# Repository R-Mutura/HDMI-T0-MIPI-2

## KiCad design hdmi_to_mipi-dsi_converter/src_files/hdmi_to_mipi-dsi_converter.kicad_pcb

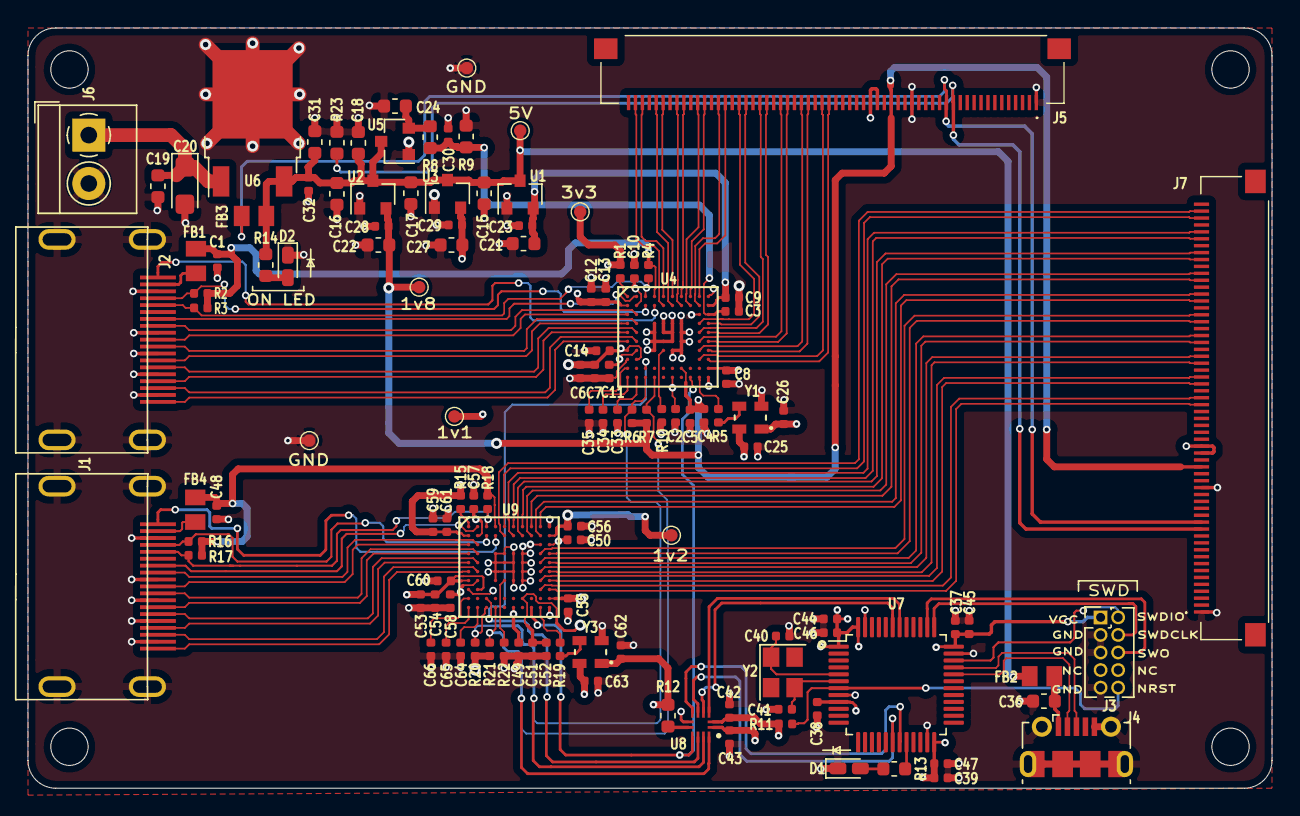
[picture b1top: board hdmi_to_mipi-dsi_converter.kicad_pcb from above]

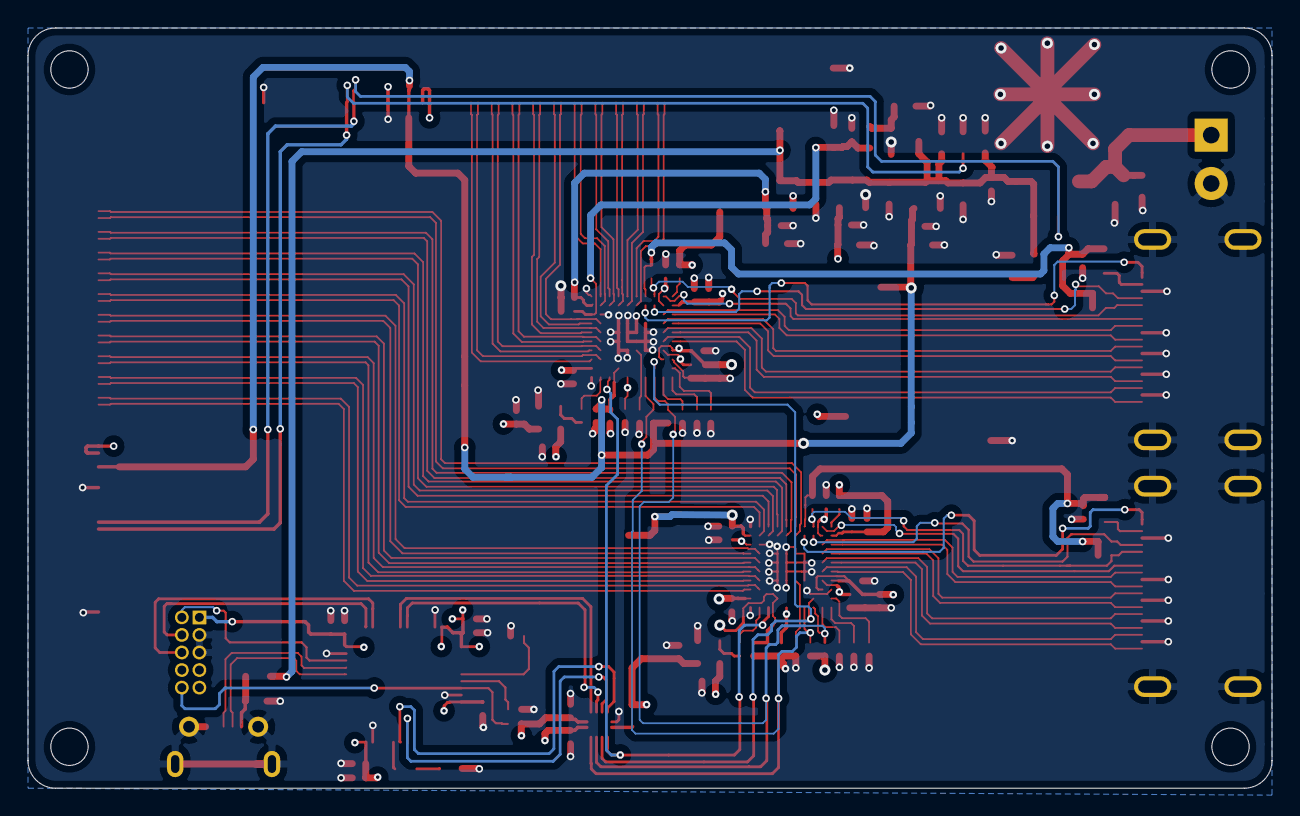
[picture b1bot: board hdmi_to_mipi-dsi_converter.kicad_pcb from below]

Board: 4 copper layers, 90.0 x 55.0 mm, 125 parts (4 on the bottom side), 113 nets.

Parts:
C1, C3, C5, C7, C9, C11, C13, C14, C32, C48, C50, C52, C54, C56, C58, C60, C61: 10n; C_0402_1005Metric
C2, C4, C6, C8, C10, C12, C23, C25, C28, C29, C30, C33, C34, C35, C37, C38, C39, C42, C43, C49, C51, C53, C55, C57, C59, C62, C64, C65, C66: 0.1u; C_0402_1005Metric
C15, C16, C17, C18, C21, C22, C24, C27, C36: 10u; C_0603_1608Metric
C19, C31: 0.1u; C_0603_1608Metric
C20: 10u; CP_EIA-3216-18_Kemet-A
C26, C63: 0.01u; C_0402_1005Metric
C40, C41: 18p; C_0402_1005Metric
C44, C45: 10u; C_0402_1005Metric
C46, C47: 4.7u; C_0402_1005Metric
D1, D2: LED_Small; LED_0603_1608Metric_Castellated
FB1, FB4: Ferrite_Bead_Small; BEADC2012X105N
FB2, FB3: BLM21PG220SN1; BEADC2012X105N
H1, H2, H3, H4: MountingHole; MountingHole_2.7mm_M2.5
J1, J2: HDMI-019S
J3: Conn_02x05_Odd_Even; PinHeader_2x05_P1.27mm_Vertical
J4: USB_B_Micro; USB_Micro-B_Molex-105017-0001
J5, J7: XF2M60151AH
J6: Conn_01x02; TerminalBlock_4Ucon_1x02_P3.50mm_Horizontal
R1, R10, R15, R22: 2k; R_0402_1005Metric
R2, R3, R4, R16, R17, R18: 47k; R_0402_1005Metric
R5, R19: 33R; R_0402_1005Metric
R6, R7, R11, R20, R21: 10k; R_0402_1005Metric
R8: 4k; R_0603_1608Metric
R9: 2k; R_0603_1608Metric
R12: 47k; R_0603_1608Metric
R13, R14: 1k; R_0603_1608Metric
R23: 0R; R_0603_1608Metric
TP1, TP2, TP3, TP4, TP5, TP6, TP7: TestPoint; TestPoint_Pad_D0.9mm
U1: MCP1700-1202E_SOT23; SOT-23
U2: MCP1700-1802E_SOT23; SOT-23
U3, U5: MCP1700-3302E_SOT23; SOT-23
U4, U9: TC358870XBG_NOK_; VFBGA-80_7x7mm_Pitch0.65mm
U6: MC78M05_TO252; TO-252-2
U7: STM32F103C8Tx; LQFP-48_7x7mm_P0.5mm
U8: FXMA2104UMX; QFN40P180X180X55-12N
Y1, Y3: CRYSTAL_48MHZ; DSC6101JI2A-048.0000
Y2: 8MHz; Crystal_SMD_3225-4Pin_3.2x2.5mm

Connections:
+1V1: C2.1, C3.1, C10.1, C11.1, C30.1, C49.1, C50.1, C57.1, C58.1, R8.2, R9.1, TP5.1, U4.B2, U4.C10, U4.G2, U4.K6, U9.B2, U9.C10, U9.G2, U9.K6
+1V2: C8.1, C9.1, C21.1, C23.1, C55.1, C56.1, TP7.1, U1.2, U4.B10, U4.J10, U9.B10, U9.J10
+1V8: C4.1, C5.1, C22.1, C28.1, C43.1, C51.1, C52.1, J5.22, J7.22, R6.2, R7.2, R20.2, R21.2, TP6.1, U2.2, U4.J7, U8.1, U9.J7
+3V3: C6.1, C7.1, C12.1, C13.1, C14.1, C25.1, C26.1, C27.1, C29.1, C37.1, C38.1, C39.1, C42.1, C44.1, C45.1, C46.1, C47.1, C53.1, C54.1, C59.1, C60.1, C61.1, C62.1, C63.1, J3.1, J5.24, J5.25, J7.24, J7.25, R1.2, R11.1, R12.2, R15.2, TP1.1, U3.2, U4.B1, U4.G1, U4.H2, U7.1, U7.9, U7.24, U7.36, U7.48, U8.2, U9.B1, U9.G1, U9.H2, Y1.1, Y1.4, Y3.1, Y3.4
+5V: C15.1, C16.1, C17.1, C18.1, C31.1, C32.1, FB2.1, FB3.2, R14.1, TP2.1, U1.3, U2.3, U3.3, U5.3, U6.3
/CDSI0_TX_D0_N: J5.32, U4.H9
/CDSI0_TX_D0_P: J5.31, U4.H10
/CDSI0_TX_D1_N: J5.35, U4.G9
/CDSI0_TX_D1_P: J5.34, U4.G10
/CDSI0_TX_D2_N: J5.41, U4.E9
/CDSI0_TX_D2_P: J5.40, U4.E10
/CDSI0_TX_D3_N: J5.44, U4.D9
/CDSI0_TX_D3_P: J5.43, U4.D10
/CDSI0_TX_DC_N: J5.38, U4.F9
/CDSI0_TX_DC_P: J5.37, U4.F10
/CDSI1_TX_D0_N: J5.47, U4.B9
/CDSI1_TX_D0_P: J5.46, U4.A9
/CDSI1_TX_D1_N: J5.50, U4.B8
/CDSI1_TX_D1_P: J5.49, U4.A8
/CDSI1_TX_D2_N: J5.56, U4.B6
/CDSI1_TX_D2_P: J5.55, U4.A6
/CDSI1_TX_D3_N: J5.59, U4.B5
/CDSI1_TX_D3_P: J5.58, U4.A5
/CDSI1_TX_DC_N: J5.53, U4.B7
/CDSI1_TX_DC_P: J5.52, U4.A7
/CEC_OUT: J2.13, U4.A2
/DDC_SCL: J2.15, R3.1, R4.1, U4.A3
/DDC_SDA: J2.16, R2.1, U4.B3
/HDMIC_N: J2.12, U4.C2
/HDMIC_P: J2.10, U4.C1
/HDMID0_N: J2.9, U4.D2
/HDMID0_P: J2.7, U4.D1
/HDMID1_N: J2.6, U4.E2
/HDMID1_P: J2.4, U4.E1
/HDMID2_N: J2.3, U4.F2
/HDMID2_P: J2.1, U4.F1
/HDMI_5V: C1.1, FB1.2, R2.2, R3.2, R4.2, U4.A4
/HDMI_HPD: J2.19, U4.B4
/hdmi_mipi_2/CDSI0_TX_D0_N: J7.32, U9.H9
/hdmi_mipi_2/CDSI0_TX_D0_P: J7.31, U9.H10
/hdmi_mipi_2/CDSI0_TX_D1_N: J7.35, U9.G9
/hdmi_mipi_2/CDSI0_TX_D1_P: J7.34, U9.G10
/hdmi_mipi_2/CDSI0_TX_D2_N: J7.41, U9.E9
/hdmi_mipi_2/CDSI0_TX_D2_P: J7.40, U9.E10
/hdmi_mipi_2/CDSI0_TX_D3_N: J7.44, U9.D9
/hdmi_mipi_2/CDSI0_TX_D3_P: J7.43, U9.D10
/hdmi_mipi_2/CDSI0_TX_DC_N: J7.38, U9.F9
/hdmi_mipi_2/CDSI0_TX_DC_P: J7.37, U9.F10
/hdmi_mipi_2/CDSI1_TX_D0_N: J7.47, U9.B9
/hdmi_mipi_2/CDSI1_TX_D0_P: J7.46, U9.A9
/hdmi_mipi_2/CDSI1_TX_D1_N: J7.50, U9.B8
/hdmi_mipi_2/CDSI1_TX_D1_P: J7.49, U9.A8
/hdmi_mipi_2/CDSI1_TX_D2_N: J7.56, U9.B6
/hdmi_mipi_2/CDSI1_TX_D2_P: J7.55, U9.A6
/hdmi_mipi_2/CDSI1_TX_D3_N: J7.59, U9.B5
/hdmi_mipi_2/CDSI1_TX_D3_P: J7.58, U9.A5
/hdmi_mipi_2/CDSI1_TX_DC_N: J7.53, U9.B7
/hdmi_mipi_2/CDSI1_TX_DC_P: J7.52, U9.A7
/hdmi_mipi_2/CEC_OUT: J1.13, U9.A2
/hdmi_mipi_2/DDC_SCL: J1.15, R17.1, R18.1, U9.A3
/hdmi_mipi_2/DDC_SDA: J1.16, R16.2, U9.B3
/hdmi_mipi_2/HDMIC_N: J1.12, U9.C2
/hdmi_mipi_2/HDMIC_P: J1.10, U9.C1
/hdmi_mipi_2/HDMID0_N: J1.9, U9.D2
/hdmi_mipi_2/HDMID0_P: J1.7, U9.D1
/hdmi_mipi_2/HDMID1_N: J1.6, U9.E2
/hdmi_mipi_2/HDMID1_P: J1.4, U9.E1
/hdmi_mipi_2/HDMID2_N: J1.3, U9.F2
/hdmi_mipi_2/HDMID2_P: J1.1, U9.F1
/hdmi_mipi_2/HDMI_5V: C48.1, FB4.2, R16.1, R17.2, R18.2, U9.A4
/hdmi_mipi_2/HDMI_HPD: J1.19, U9.B4
/hdmi_mipi_2/refclk: R19.1, U9.K9
/hdmi_mipi_2/test: R22.2, U9.G5
/mcu_ctrl/DIFF_N: J4.2, U7.32
/mcu_ctrl/DIFF_P: J4.3, U7.33
/mcu_ctrl/INT: U7.18, U8.5
/mcu_ctrl/LED: R13.1, U7.20
/mcu_ctrl/NRST: J3.10, R11.2, U7.7
/mcu_ctrl/OSCIN: C40.1, U7.5, Y2.1
/mcu_ctrl/OSCOUT: C41.1, U7.6, Y2.3
/mcu_ctrl/RST: U7.19, U8.6
/mcu_ctrl/SCL: U7.42, U8.3
/mcu_ctrl/SDA: U7.43, U8.4
/mcu_ctrl/SWDCLK: J3.4, U7.37
/mcu_ctrl/SWDIO: J3.2, U7.34
/mcu_ctrl/SWO: J3.6, U7.38
/power/24VIN: C19.1, C20.1, J6.1, U6.1
/refclk: R5.1, U4.K9
/test: R10.2, U4.G5
CTRL_INT: U4.J3, U8.10, U9.J3
GND: C1.2, C2.2, C3.2, C4.2, C5.2, C6.2, C7.2, C8.2, C9.2, C10.2, C11.2, C12.2, C13.2, C14.2, C15.2, C16.2, C17.2, C18.2, C19.2, C20.2, C21.2, C22.2, C23.2, C24.2, C25.2, C26.2, C27.2, C28.2, C29.2, C30.2, C31.2, C32.2, C33.2, C34.2, C35.2, C36.2, C37.2, C38.2, C39.2, C40.2, C41.2, C42.2, C43.2, C44.2, C45.2, C46.2, C47.2, C48.2, C49.2, C50.2, C51.2, C52.2, C53.2, C54.2, C55.2, C56.2, C57.2, C58.2, C59.2, C60.2, C61.2, C62.2, C63.2, C64.2, C65.2, C66.2, D1.1, D2.1, J1.2, J1.5, J1.8, J1.11, J1.17, J1.SH, J2.2, J2.5, J2.8, J2.11, J2.17, J2.SH, J3.3, J3.5, J3.9, J4.5, J4.6, J5.1, J5.19, J6.2, J7.1, J7.19, R9.2, R10.1, R22.1, R23.1, TP3.1, TP4.1, U1.1, U2.1, U3.1, U4.A10, U4.C9, U4.D4, U4.D5, U4.D6, U4.D7, U4.E4, U4.E5, U4.E6, U4.E7, U4.F4, U4.F5, U4.F6, U4.F7, U4.G4, U4.G6, U4.G7, U4.H1, U4.K10, U5.1, U6.2, U7.8, U7.23, U7.35, U7.47, U8.7, U9.A10, U9.C9, U9.D4, U9.D5, U9.D6, U9.D7, U9.E4, U9.E5, U9.E6, U9.E7, U9.F4, U9.F5, U9.F6, U9.F7, U9.G4, U9.G6, U9.G7, U9.H1, U9.K10, Y1.2, Y3.2
I2C_SCL: R7.1, R21.1, U4.K4, U8.12, U9.K4
I2C_SDA: R6.1, R20.1, U4.K3, U8.11, U9.K3
unnamed: C24.1, R8.1, U5.2
unnamed: C33.1, U4.K2
unnamed: C34.1, U4.K1
unnamed: C35.1, U4.J1
unnamed: C64.1, U9.K2
unnamed: C65.1, U9.K1
unnamed: C66.1, U9.J1
unnamed: D1.2, R13.2
unnamed: D2.2, R14.2
unnamed: FB1.1, J2.18
unnamed: FB4.1, J1.18
unnamed: R1.1, U4.A1
unnamed: R5.2, Y1.3
unnamed: R12.1, U8.8
unnamed: R15.1, U9.A1
unnamed: R19.2, Y3.3
RESET_N: U4.K8, U8.9, U9.K8
VBUS: C36.1, FB2.2, J4.1
VSN: J5.13, J7.13, R23.2
VSP: FB3.1, J5.14, J7.14

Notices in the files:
parts and their libraries:
Copyright 2016 Accelerated Designs. All rights reserved.
